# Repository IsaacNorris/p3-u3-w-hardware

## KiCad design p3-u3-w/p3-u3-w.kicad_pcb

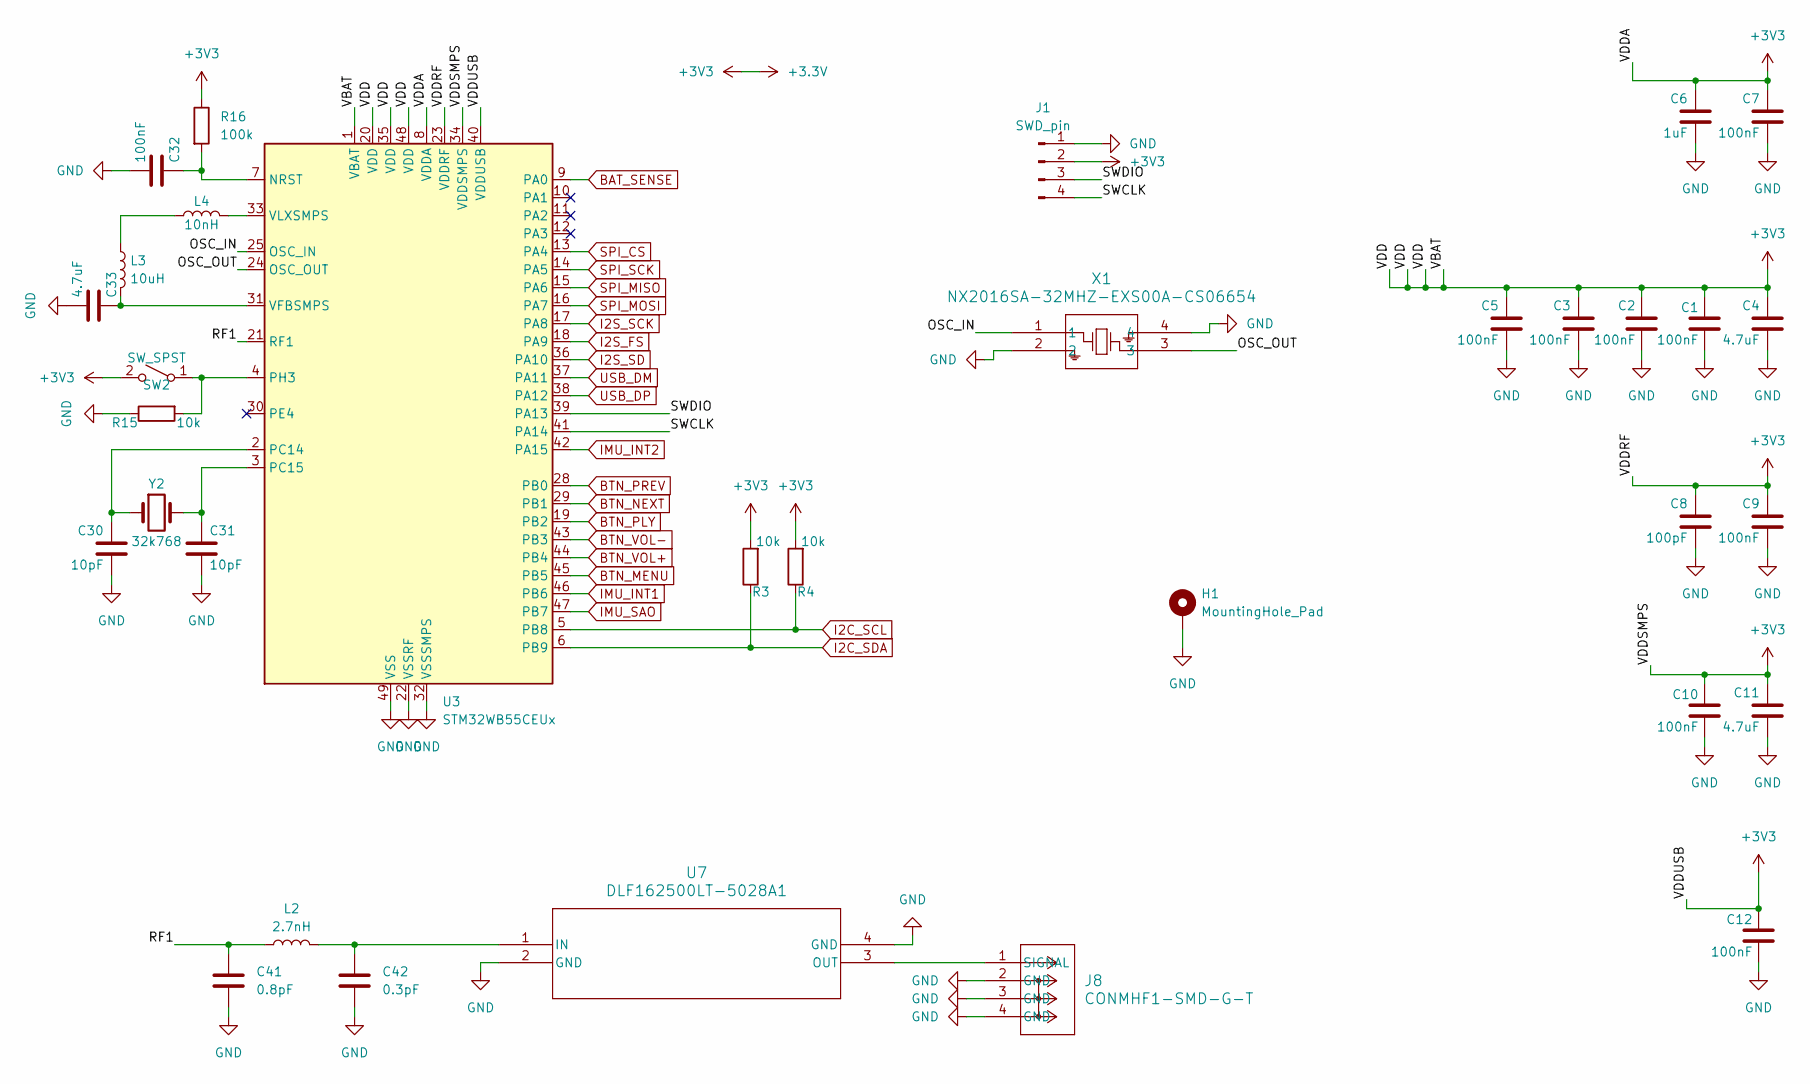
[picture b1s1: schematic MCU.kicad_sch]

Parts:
C1, C2, C3, C5, C7, C9, C10, C12, C32: 100nF; C_0402_1005Metric
C4, C11, C33: 4.7uF; C_0402_1005Metric
C6: 1uF; C_0402_1005Metric
C8: 100pF; C_0402_1005Metric
C30, C31: 10pF; C_0402_1005Metric
C41: 0.8pF; C_0402_1005Metric
C42: 0.3pF; C_0402_1005Metric
H1: MountingHole_Pad; MountingHole_2.2mm_M2_Pad
J1: SWD_pin; PinHeader_1x04_P1.00mm_Vertical
J8: CONMHF1-SMD-G-T; COAX3_CONMHF1-SMD-G-T_TEC
L2: 2.7nH; L_0603_1608Metric
L3: 10uH; L_0603_1608Metric
L4: 10nH; L_0603_1608Metric
R3, R4, R15: 10k; R_0402_1005Metric
R16: 100k; R_0402_1005Metric
SW2: SW_SPST; Panasonic_EVQPUL_EVQPUC
U3: STM32WB55CEUx; QFN-48-1EP_7x7mm_P0.5mm_EP5.6x5.6mm
U7: DLF162500LT-5028A1; DLF-4_1P6X0P8
X1: NX2016SA-32MHZ-EXS00A-CS06654; NX2016SA_NDK
Y2: 32k768; Crystal_SMD_3215-2Pin_3.2x1.5mm

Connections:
+3.3V: C1.2, C2.2, C3.2, C4.2, C5.2, C6.2, C7.2, C8.2, C9.2, C10.2, C11.2, C12.2, J1.2, R3.2, R4.2, R16.1, SW2.2 (B), U3.1 (VBAT), U3.8 (VDDA), U3.20 (VDD), U3.23 (VDDRF), U3.34 (VDDSMPS), U3.35 (VDD), U3.40 (VDDUSB), U3.48 (VDD); also elsewhere on the board
/MCU/OSC_IN: U3.25 (OSC_IN), X1.1
/MCU/OSC_OUT: U3.24 (OSC_OUT), X1.3
/MCU/RF1: C41.1, L2.1, U3.21 (RF1)
/MCU/SWCLK: J1.4, U3.41 (PA14)
/MCU/SWDIO: J1.3, U3.39 (PA13)
BAT_SENSE: U3.9 (PA0); also elsewhere on the board
BTN_MENU: U3.45 (PB5); also elsewhere on the board
BTN_NEXT: U3.29 (PB1); also elsewhere on the board
BTN_PLY: U3.19 (PB2); also elsewhere on the board
BTN_PREV: U3.28 (PB0); also elsewhere on the board
BTN_VOL+: U3.44 (PB4); also elsewhere on the board
BTN_VOL-: U3.43 (PB3); also elsewhere on the board
GND: C1.1, C2.1, C3.1, C4.1, C5.1, C6.1, C7.1, C8.1, C9.1, C10.1, C11.1, C12.1, C30.1, C31.1, C32.1, C33.1, C41.2, C42.2, H1.1 (1_1), J1.1, J8.2 (GND), J8.3 (GND), J8.4 (GND), R15.1, U3.22 (VSSRF), U3.32 (VSSSMPS), U3.49 (VSS), U7.2 (GND), U7.4 (GND), X1.2, X1.4; also elsewhere on the board
I2C_SCL: R4.1, U3.5 (PB8); also elsewhere on the board
I2C_SDA: R3.1, U3.6 (PB9); also elsewhere on the board
I2S_FS: U3.18 (PA9); also elsewhere on the board
I2S_SCK: U3.17 (PA8); also elsewhere on the board
I2S_SD: U3.36 (PA10); also elsewhere on the board
IMU_INT1: U3.46 (PB6); also elsewhere on the board
IMU_INT2: U3.42 (PA15); also elsewhere on the board
IMU_SAO: U3.47 (PB7); also elsewhere on the board
unnamed: J8.1 (SIGNAL), U7.3 (OUT)
unnamed: L3.1, L4.1
unnamed: R15.2, SW2.1 (A), U3.4 (PH3)
unnamed: C32.2, R16.2, U3.7 (NRST)
unnamed: C30.2, U3.2 (PC14), Y2.1
unnamed: C31.2, U3.3 (PC15), Y2.2
unnamed: C33.2, L3.2, U3.31 (VFBSMPS)
unnamed: L4.2, U3.33 (VLXSMPS)
unnamed: C42.1, L2.2, U7.1 (IN)
SPI_CS: U3.13 (PA4); also elsewhere on the board
SPI_MISO: U3.15 (PA6); also elsewhere on the board
SPI_MOSI: U3.16 (PA7); also elsewhere on the board
SPI_SCK: U3.14 (PA5); also elsewhere on the board
USB_D+: U3.38 (PA12); also elsewhere on the board
USB_D-: U3.37 (PA11); also elsewhere on the board

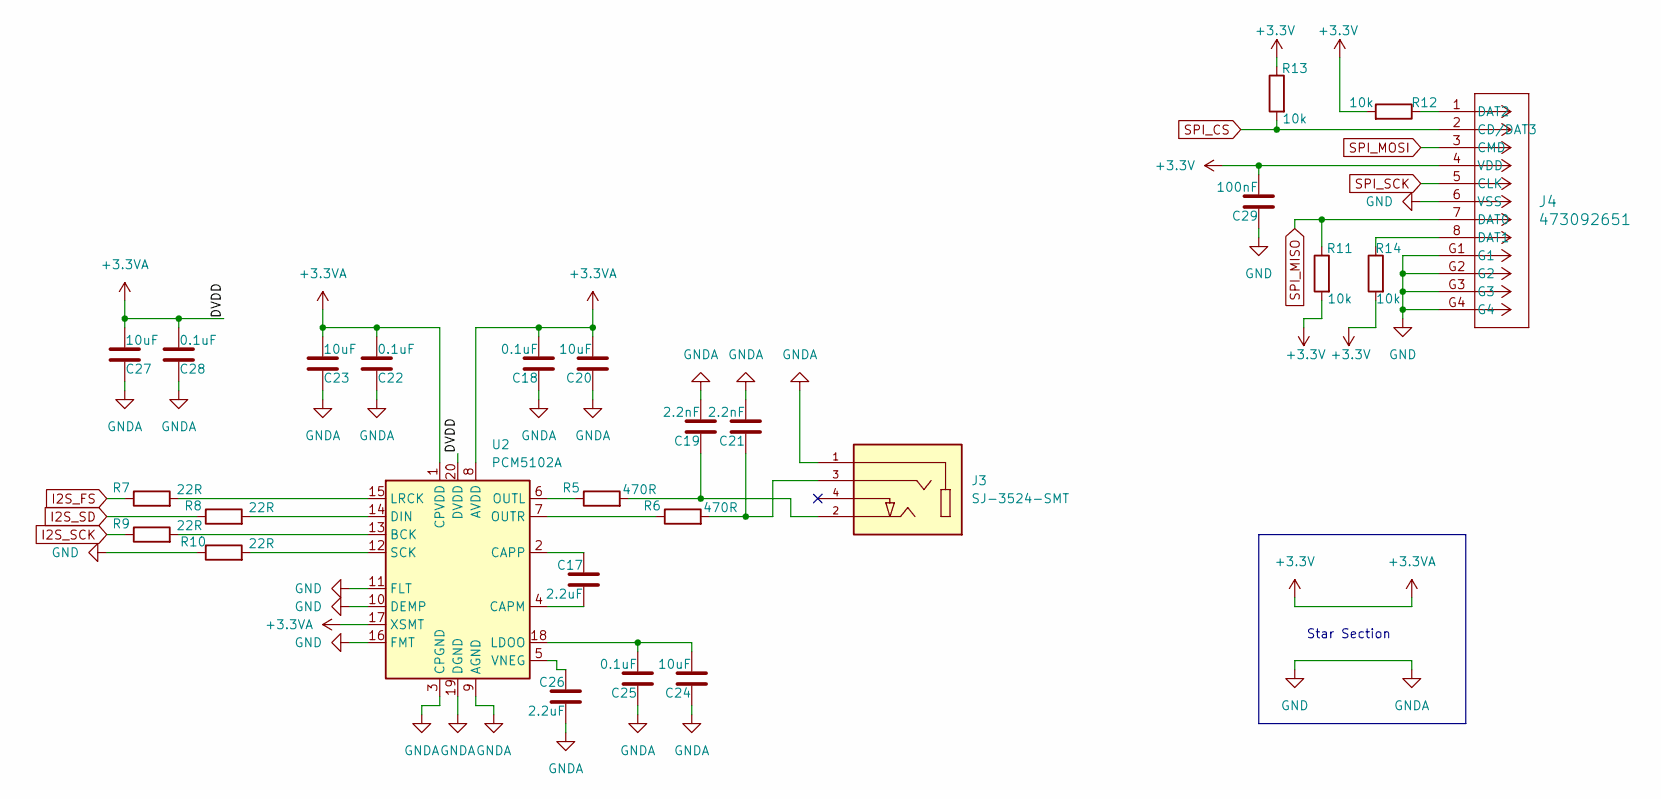
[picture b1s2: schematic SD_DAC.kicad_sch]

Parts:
C17, C26: 2.2uF; C_0402_1005Metric
C18, C22, C25, C28: 0.1uF; C_0402_1005Metric
C19, C21: 2.2nF; C_0402_1005Metric
C20, C23, C24, C27: 10uF; C_0402_1005Metric
C29: 100nF; C_0402_1005Metric
J3: SJ-3524-SMT; CUI_SJ-3524-SMT; PARTREV 1.03
J4: 473092651; CONN12_47309-2651_MOL
R5, R6: 470R; R_0402_1005Metric
R7, R8, R9, R10: 22R; R_0402_1005Metric
R11, R12, R13, R14: 10k; R_0402_1005Metric
U2: PCM5102A; TSSOP-20_4.4x6.5mm_P0.65mm

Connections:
+3.3V: C18.2, C20.2, C22.2, C23.2, C27.2, C28.2, C29.2, J4.4 (VDD), R11.2, R12.2, R13.1, R14.2, U2.1 (CPVDD), U2.8 (AVDD), U2.17 (XSMT), U2.20 (DVDD); also elsewhere on the board
GND: C18.1, C19.2, C20.1, C21.2, C22.1, C23.1, C24.1, C25.1, C26.2, C27.1, C28.1, C29.1, J3.1, J4.6 (VSS), J4.G1, J4.G2, J4.G3, J4.G4, R10.1, U2.3 (CPGND), U2.9 (AGND), U2.10 (DEMP), U2.11 (FLT), U2.16 (FMT), U2.19 (DGND); also elsewhere on the board
I2S_FS: R7.1; also elsewhere on the board
I2S_SCK: R9.1; also elsewhere on the board
I2S_SD: R8.1; also elsewhere on the board
unnamed: C19.1, J3.2, R5.2
unnamed: C21.1, J3.3, R6.2
unnamed: J4.8 (DAT1), R14.1
unnamed: J4.1 (DAT2), R12.1
unnamed: R9.2, U2.13 (BCK)
unnamed: C17.2, U2.4 (CAPM)
unnamed: C17.1, U2.2 (CAPP)
unnamed: R8.2, U2.14 (DIN)
unnamed: C24.2, C25.2, U2.18 (LDOO)
unnamed: R7.2, U2.15 (LRCK)
unnamed: R5.1, U2.6 (OUTL)
unnamed: R6.1, U2.7 (OUTR)
unnamed: R10.2, U2.12 (SCK)
unnamed: C26.1, U2.5 (VNEG)
SPI_CS: J4.2 (CD/DAT3), R13.2; also elsewhere on the board
SPI_MISO: J4.7 (DAT0), R11.1; also elsewhere on the board
SPI_MOSI: J4.3 (CMD); also elsewhere on the board
SPI_SCK: J4.5 (CLK); also elsewhere on the board

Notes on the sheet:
Star Section

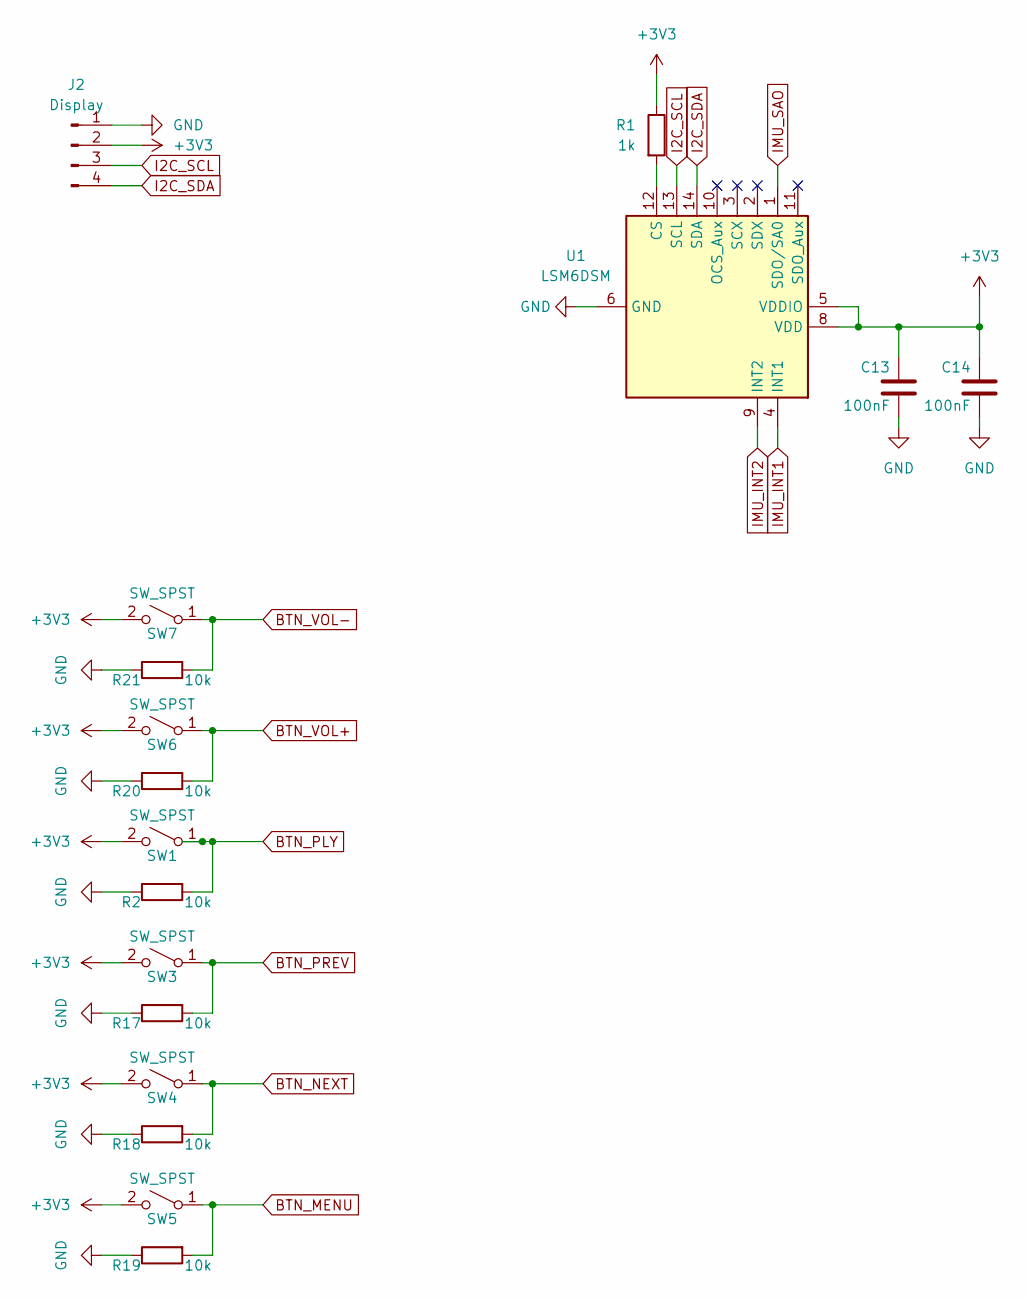
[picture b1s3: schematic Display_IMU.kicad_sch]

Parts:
C13, C14: 100nF; C_0402_1005Metric
J2: Display; PinHeader_1x04_P2.54mm_Vertical
R1: 1k; R_0402_1005Metric
R2, R17, R18, R19, R20, R21: 10k; R_0402_1005Metric
SW1, SW3, SW4, SW5, SW6, SW7: SW_SPST; Panasonic_EVQPUL_EVQPUC
U1: LSM6DSM; LGA-14_3x2.5mm_P0.5mm_LayoutBorder3x4y

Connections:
+3.3V: C13.2, C14.2, J2.2, R1.1, SW1.2 (B), SW3.2 (B), SW4.2 (B), SW5.2 (B), SW6.2 (B), SW7.2 (B), U1.5 (VDDIO), U1.8 (VDD); also elsewhere on the board
BTN_MENU: R19.2, SW5.1 (A); also elsewhere on the board
BTN_NEXT: R18.2, SW4.1 (A); also elsewhere on the board
BTN_PLY: R2.2, SW1.1 (A); also elsewhere on the board
BTN_PREV: R17.2, SW3.1 (A); also elsewhere on the board
BTN_VOL+: R20.2, SW6.1 (A); also elsewhere on the board
BTN_VOL-: R21.2, SW7.1 (A); also elsewhere on the board
GND: C13.1, C14.1, J2.1, R2.1, R17.1, R18.1, R19.1, R20.1, R21.1, U1.6 (GND), U1.7 (GND); also elsewhere on the board
I2C_SCL: J2.3, U1.13 (SCL); also elsewhere on the board
I2C_SDA: J2.4, U1.14 (SDA); also elsewhere on the board
IMU_INT1: U1.4 (INT1); also elsewhere on the board
IMU_INT2: U1.9 (INT2); also elsewhere on the board
IMU_SAO: U1.1 (SDO/SA0); also elsewhere on the board
unnamed: R1.2, U1.12 (CS)

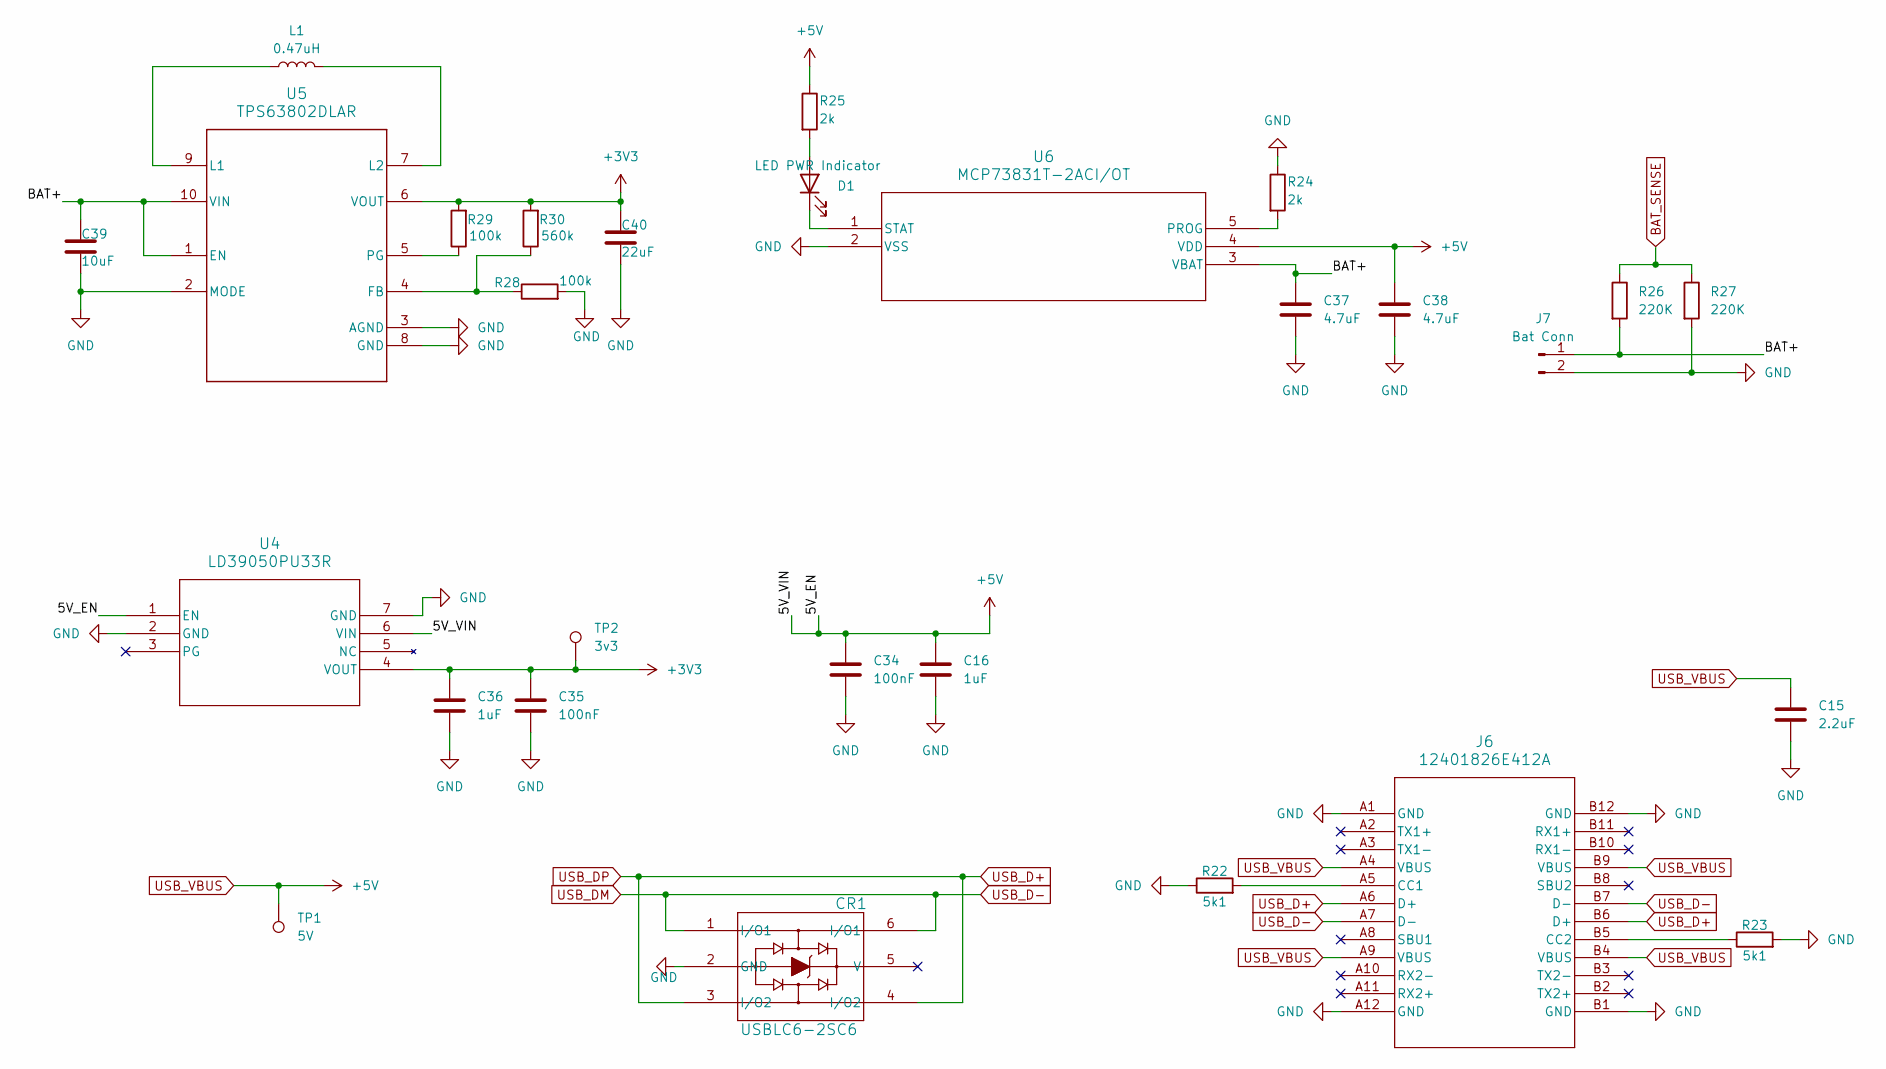
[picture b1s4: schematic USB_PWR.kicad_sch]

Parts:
C15: 2.2uF; C_0402_1005Metric
C16, C36: 1uF; C_0402_1005Metric
C34, C35: 100nF; C_0402_1005Metric
C37, C38: 4.7uF; C_0402_1005Metric
C39: 10uF; C_0402_1005Metric
C40: 22uF; C_0402_1005Metric
CR1: USBLC6-2SC6; SOT-23-6
D1: LED PWR Indicator; D_0603_1608Metric
J6: 12401826E412A; 12401826_AMP
J7: Bat Conn; PinHeader_1x02_P2.54mm_Vertical
L1: 0.47uH; L_0603_1608Metric
R22, R23: 5k1; R_0402_1005Metric
R24, R25: 2k; R_0402_1005Metric
R26, R27: 220K; R_0402_1005Metric
R28, R29: 100k; R_0402_1005Metric
R30: 560k; R_0402_1005Metric
TP1: 5V; TestPoint_Pad_D1.0mm
TP2: 3v3; TestPoint_Pad_D1.0mm
U4: LD39050PU33R; DFN6_3X3_STM
U5: TPS63802DLAR; DLA0010A
U6: MCP73831T-2ACI/OT; SOT-23-5_MC_MCH

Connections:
+3.3V: C35.1, C36.1, C40.1, R29.2, R30.2, TP2.1 (1_1), U4.4 (VOUT), U5.6 (VOUT); also elsewhere on the board
/USB_PWR/BAT+: C37.1, C39.1, J7.1, R26.2, U5.1 (EN), U5.10 (VIN), U6.3 (VBAT)
BAT_SENSE: R26.1, R27.1; also elsewhere on the board
GND: C15.2, C16.2, C34.2, C35.2, C36.2, C37.2, C38.2, C39.2, C40.2, CR1.2 (GND), J6.A1 (GND), J6.A12 (GND), J6.B1 (GND), J6.B12 (GND), J7.2, R22.1, R23.2, R24.1, R27.2, R28.2, U4.2 (GND), U4.7 (GND), U5.2 (MODE), U5.3 (AGND), U5.8 (GND), U6.2 (VSS); also elsewhere on the board
unnamed: D1.2 (A), R25.2
unnamed: D1.1 (K), U6.1 (STAT)
unnamed: J6.A5 (CC1), R22.2
unnamed: J6.B5 (CC2), R23.1
unnamed: R28.1, R30.1, U5.4 (FB)
unnamed: L1.1, U5.9 (L1)
unnamed: L1.2, U5.7 (L2)
unnamed: R29.1, U5.5 (PG)
unnamed: R24.2, U6.5 (PROG)
USB_D+: CR1.3 (I/O2), CR1.4 (I/O2), J6.A6 (D+), J6.B6 (D+); also elsewhere on the board
USB_D-: CR1.1 (I/O1), CR1.6 (I/O1), J6.A7 (D-), J6.B7 (D-); also elsewhere on the board
USB_VBUS: C15.1, C16.1, C34.1, C38.1, J6.A4 (VBUS), J6.A9 (VBUS), J6.B4 (VBUS), J6.B9 (VBUS), R25.1, TP1.1 (1_1), U4.1 (EN), U4.6 (VIN), U6.4 (VDD)

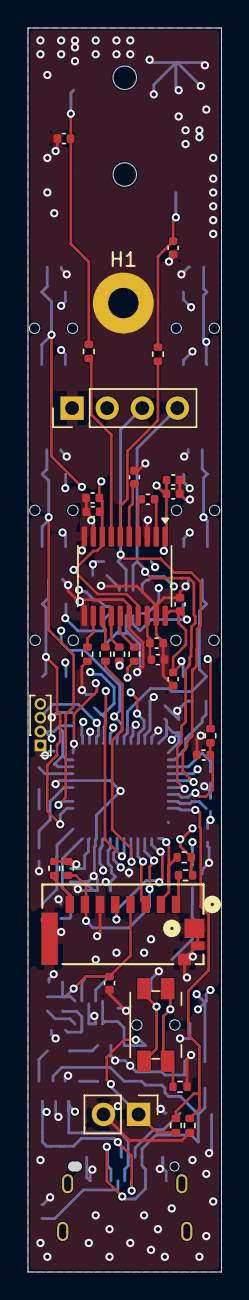
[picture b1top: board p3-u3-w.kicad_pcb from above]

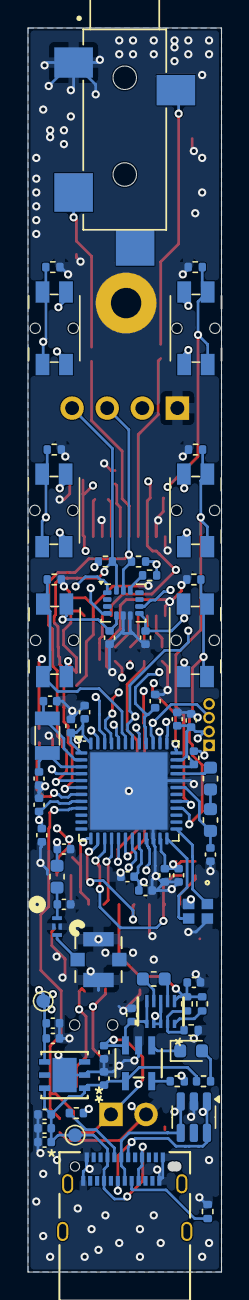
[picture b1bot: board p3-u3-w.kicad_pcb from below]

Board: 6 copper layers, 14.0 x 90.0 mm, 104 parts (69 on the bottom side), 63 nets.
